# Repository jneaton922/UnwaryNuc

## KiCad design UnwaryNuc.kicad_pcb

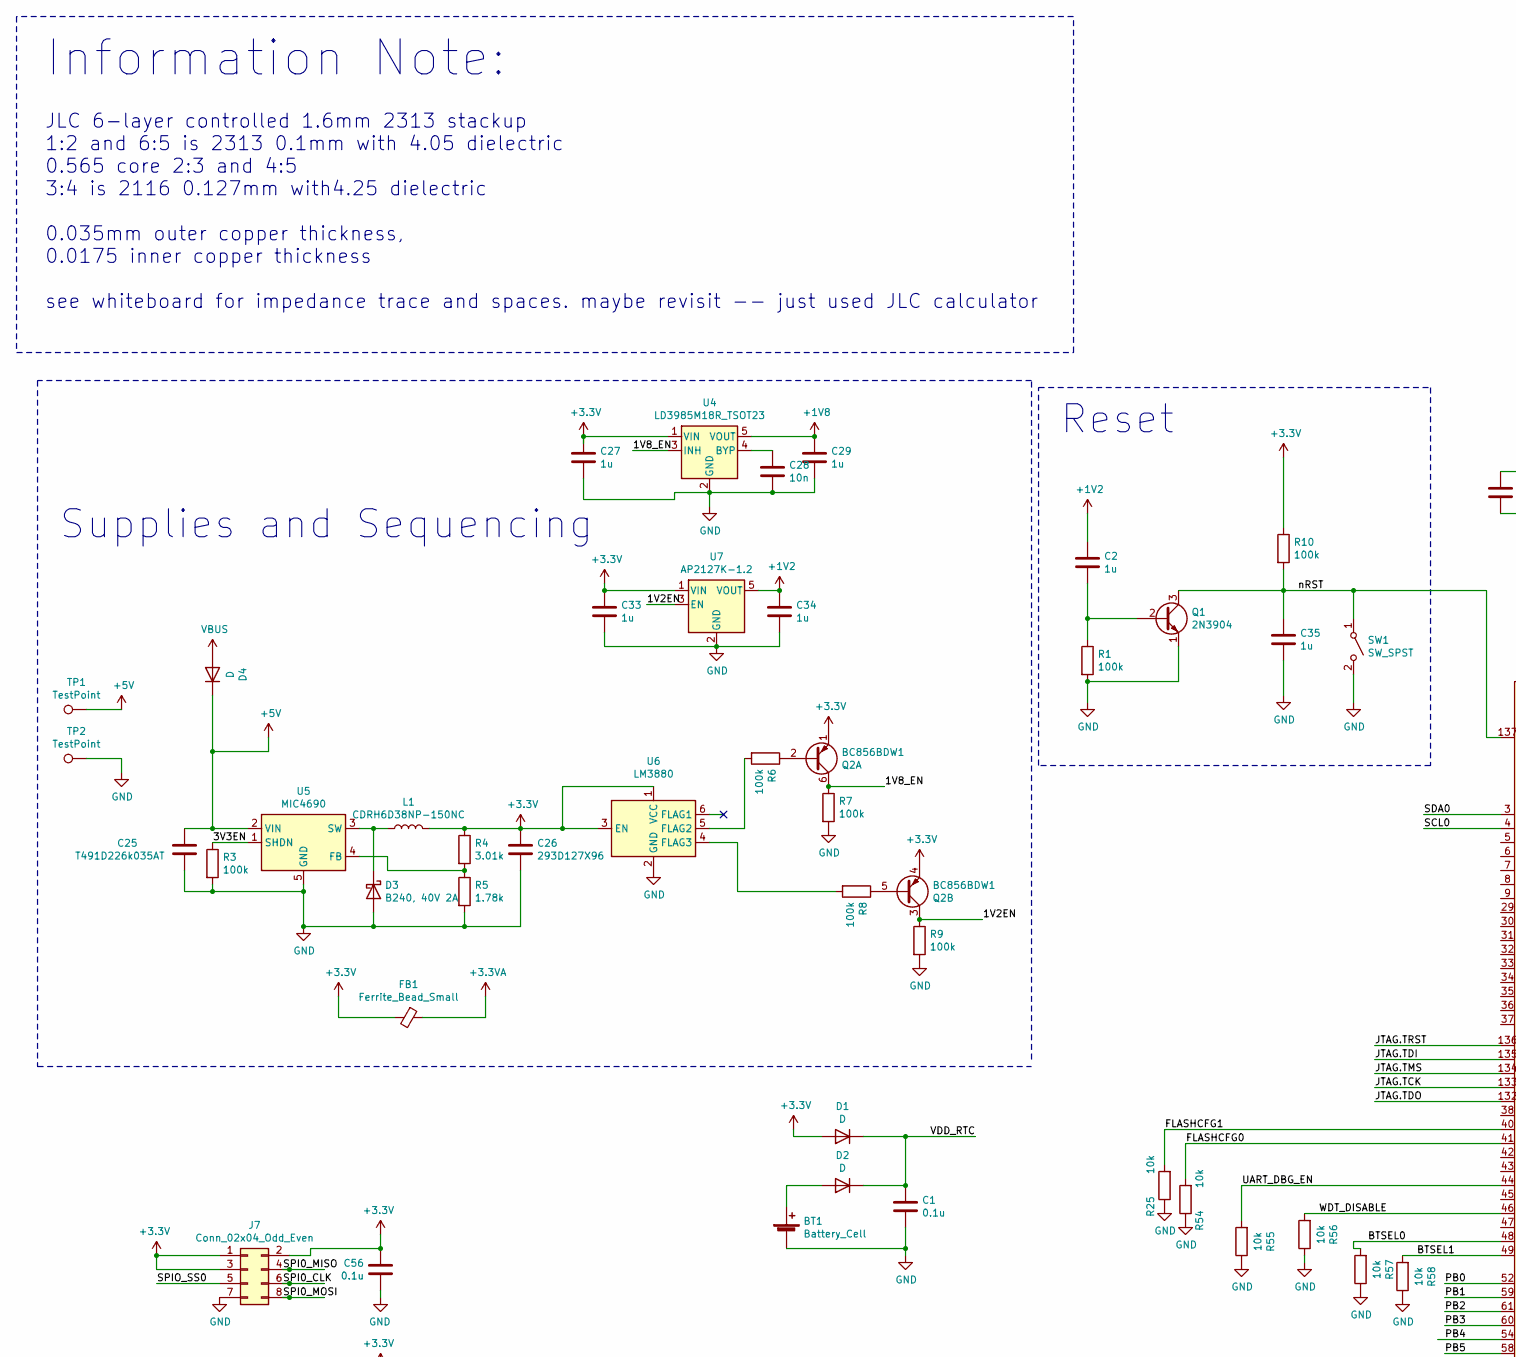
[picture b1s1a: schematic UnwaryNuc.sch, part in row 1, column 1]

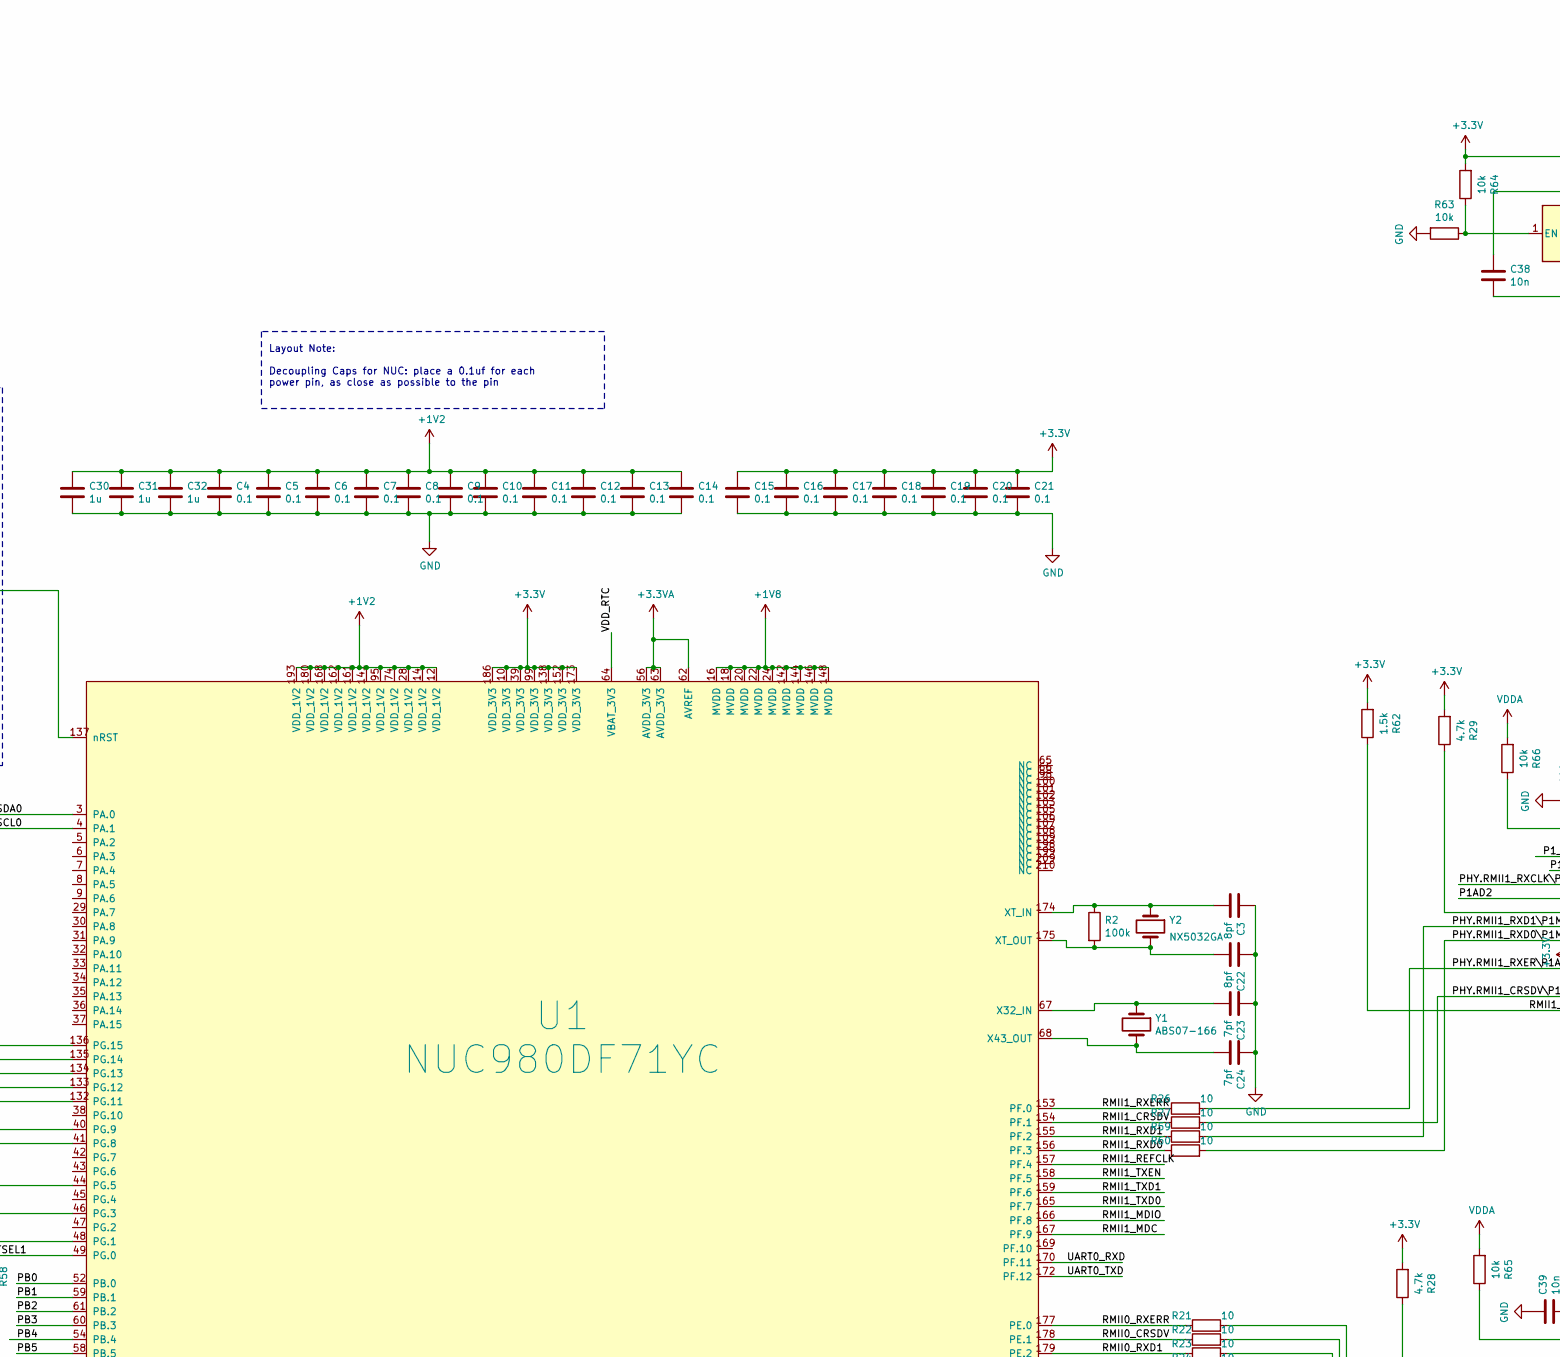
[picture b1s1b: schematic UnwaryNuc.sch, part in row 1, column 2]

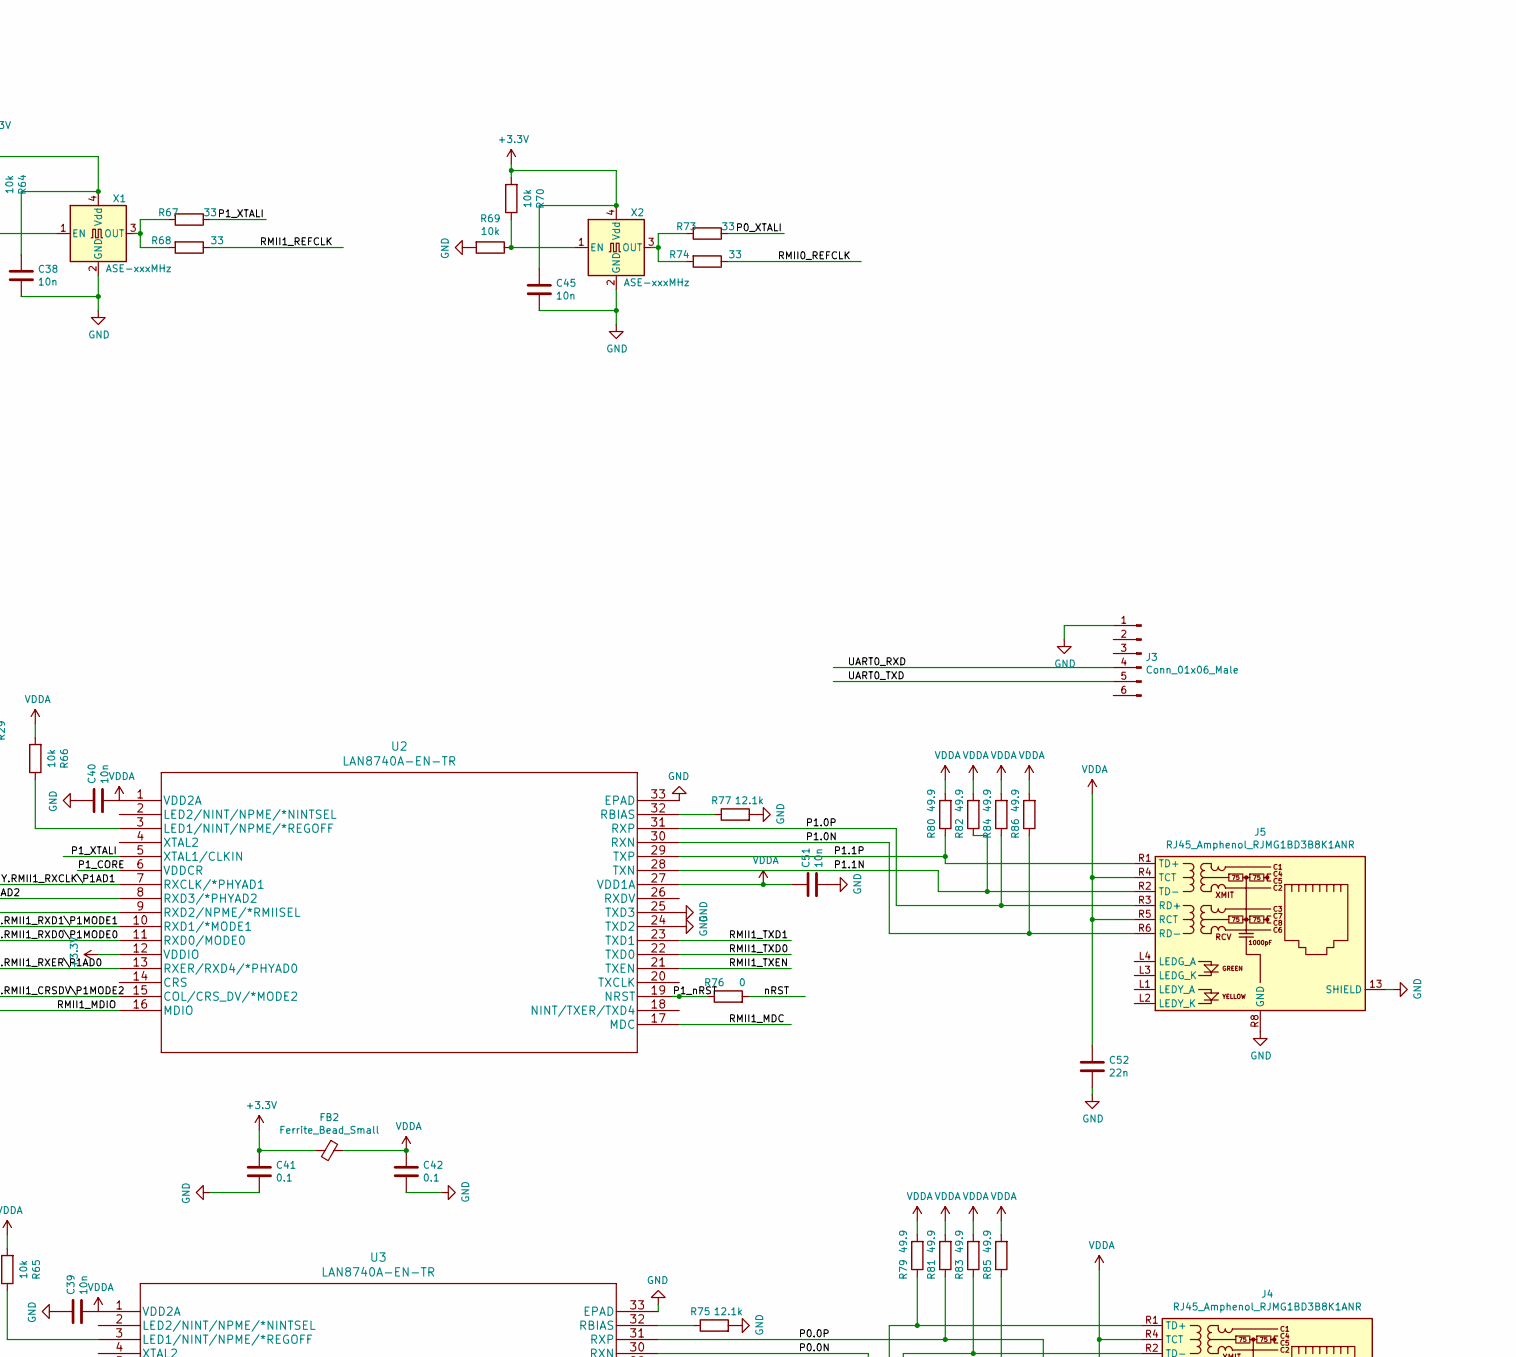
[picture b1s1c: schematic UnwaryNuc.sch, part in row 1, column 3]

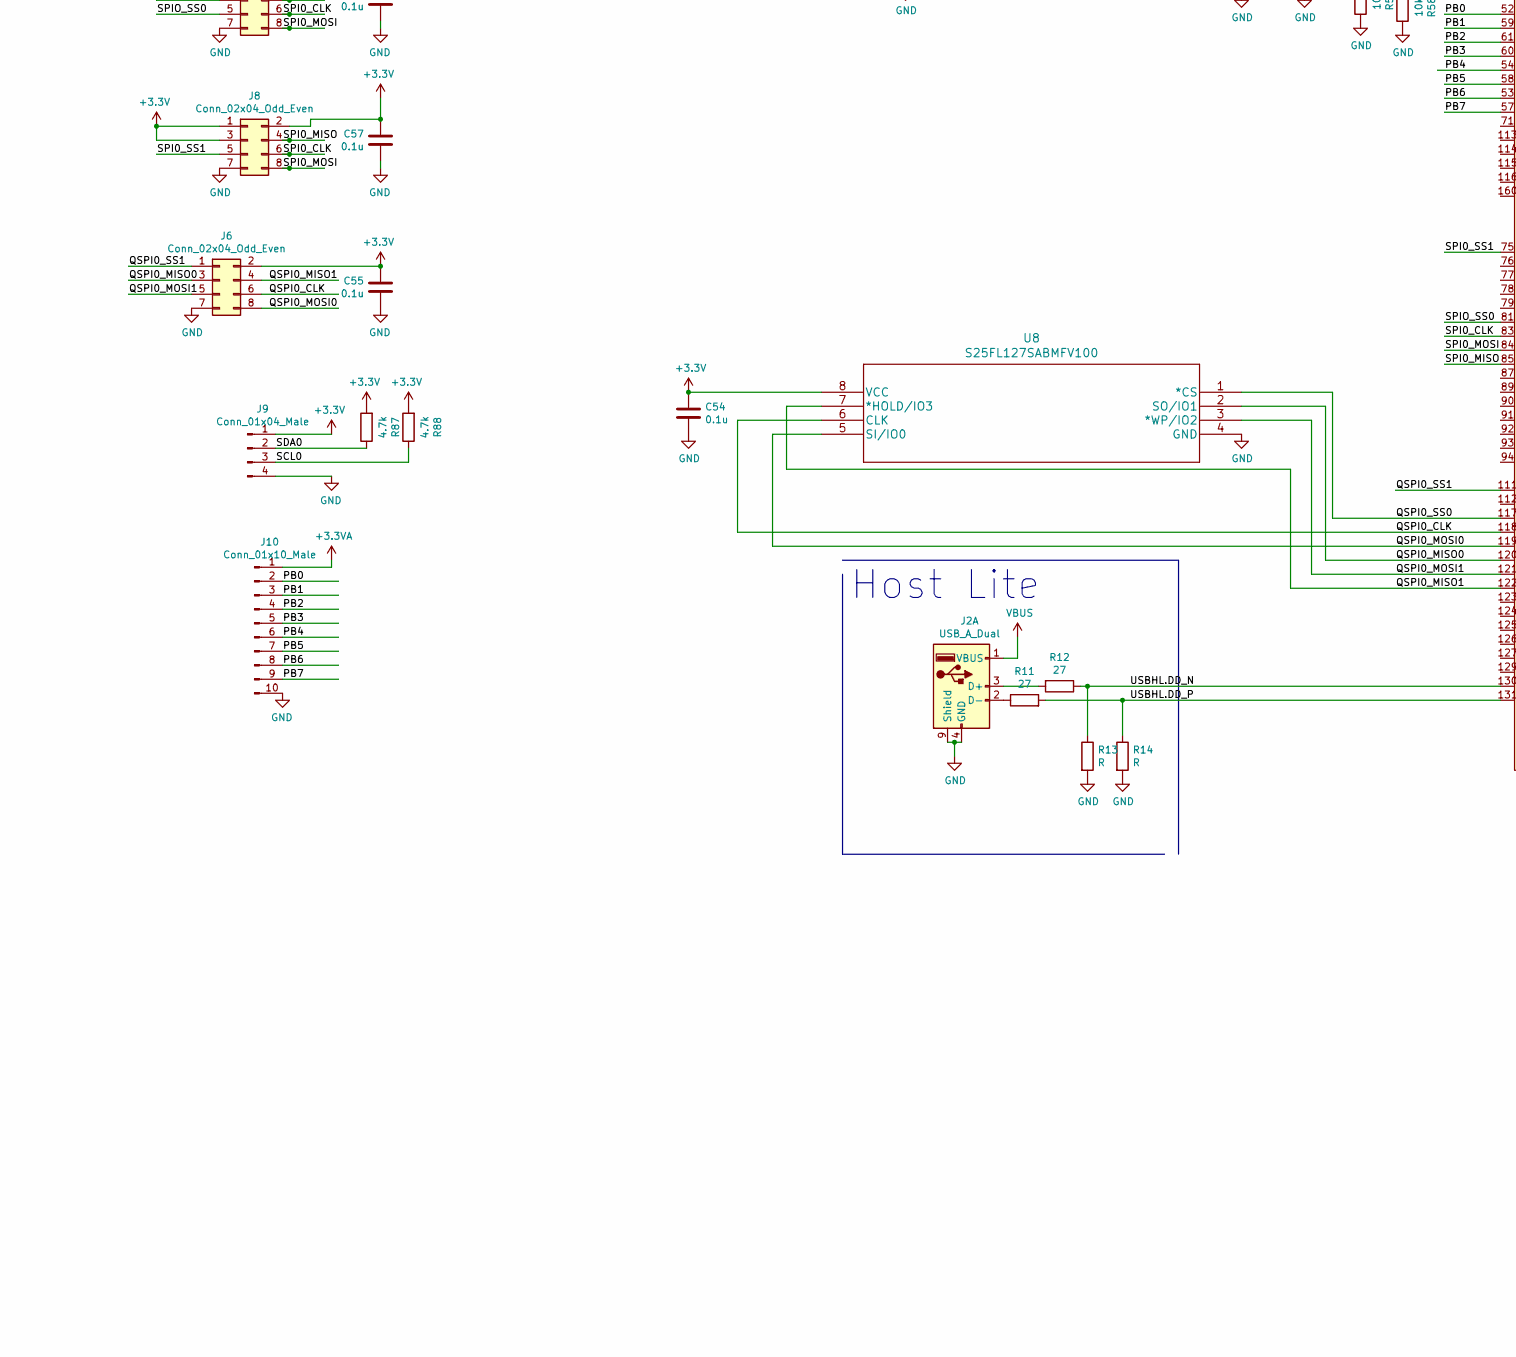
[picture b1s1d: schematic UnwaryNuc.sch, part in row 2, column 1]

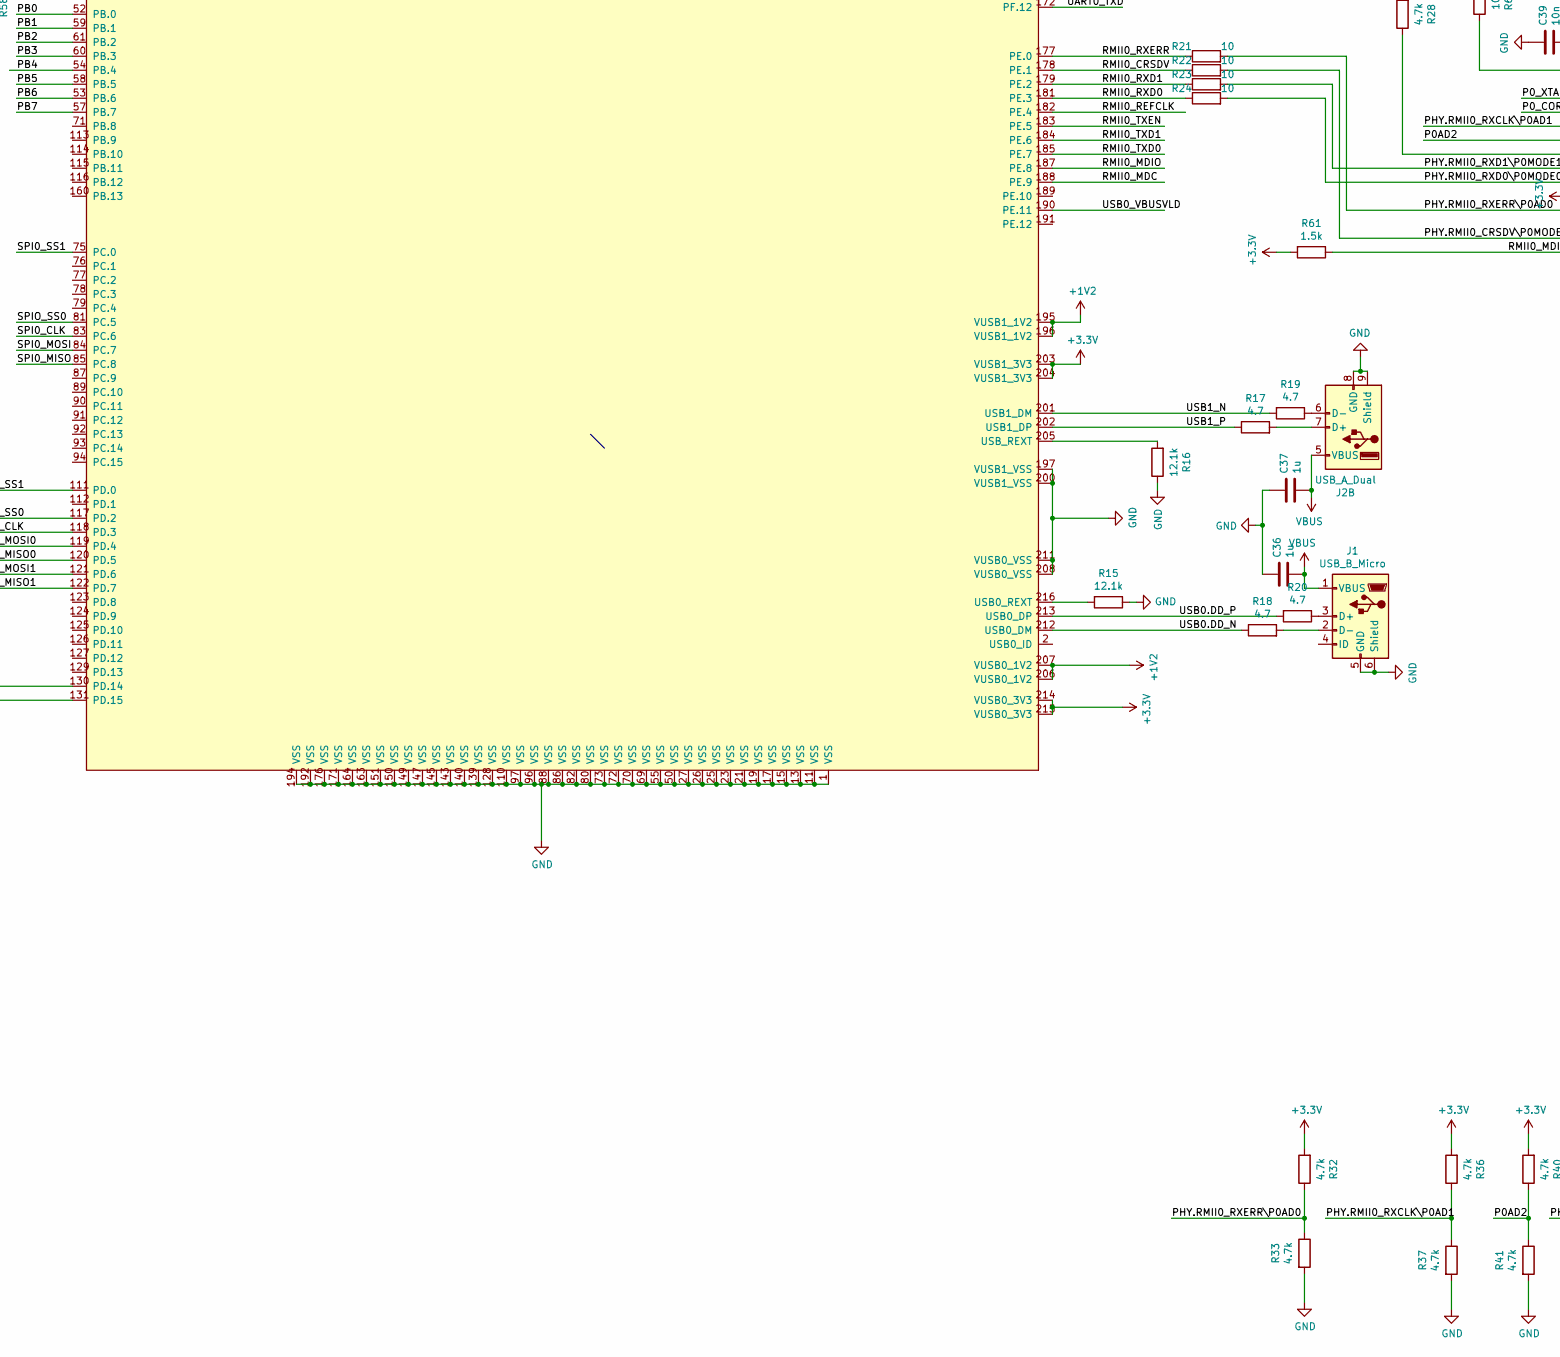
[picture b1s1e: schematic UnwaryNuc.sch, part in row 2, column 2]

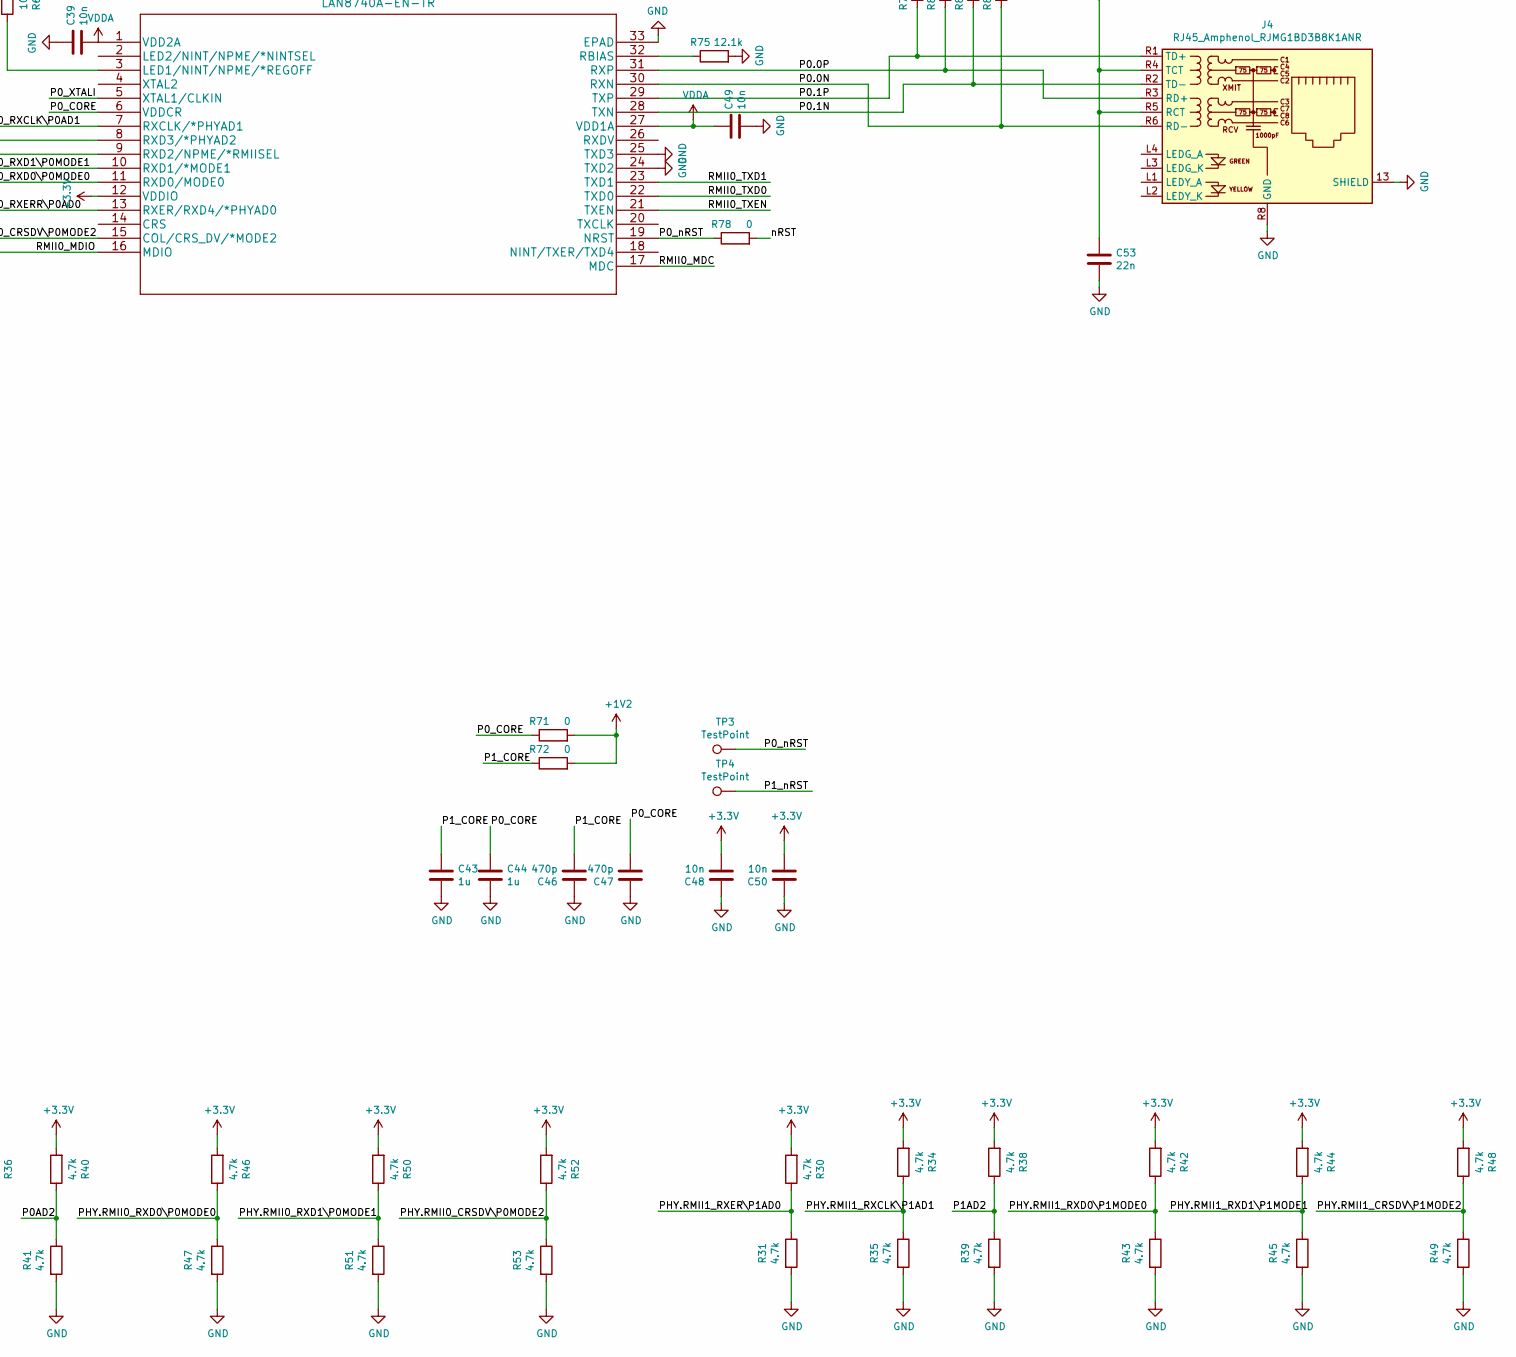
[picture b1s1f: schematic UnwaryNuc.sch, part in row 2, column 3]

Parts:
BT1: Battery_Cell; Battery_Panasonic_CR2032-VS1N_Vertical_CircularHoles
C1, C54, C55, C56, C57: 0.1u; C_1206_3216Metric_Pad1.33x1.80mm_HandSolder
C2, C27, C29, C30, C31, C32, C33, C34, C35, C36, C37, C43, C44: 1u; C_1206_3216Metric_Pad1.33x1.80mm_HandSolder
C3, C22: 8pf; C_0603_1608Metric_Pad1.08x0.95mm_HandSolder
C4, C5, C6, C7, C8, C9, C10, C11, C12, C13, C14, C15, C16, C17, C18, C19, C20, C21, C41, C42: 0.1; C_1206_3216Metric_Pad1.33x1.80mm_HandSolder
C23, C24: 7pf; C_0603_1608Metric_Pad1.08x0.95mm_HandSolder
C25: T491D226k035AT; CP_EIA-7343-15_Kemet-W_Pad2.25x2.55mm_HandSolder
C26: 293D127X96; CP_EIA-7343-43_Kemet-X_Pad2.25x2.55mm_HandSolder
C28: 10n; C_1206_3216Metric_Pad1.33x1.80mm_HandSolder
C38, C39, C40, C45, C48, C49, C50, C51: 10n; C_0603_1608Metric_Pad1.08x0.95mm_HandSolder
C46, C47: 470p; C_0603_1608Metric_Pad1.08x0.95mm_HandSolder
C52, C53: 22n; C_0805_2012Metric_Pad1.18x1.45mm_HandSolder
D1, D2, D4: D; D_SOD-523
D3: B240, 40V 2A; D_SMB_Handsoldering
FB1, FB2: Ferrite_Bead_Small; L_1206_3216Metric_Pad1.42x1.75mm_HandSolder
J1: USB_B_Micro; USB_Micro-B_Molex_47346-0001
J2: USB_A_Dual; USB_A_Wuerth_61400826021_Horizontal_Stacked
J3: Conn_01x06_Male; PinHeader_1x06_P2.54mm_Vertical
J4, J5: RJ45_Amphenol_RJMG1BD3B8K1ANR
J6, J7, J8: Conn_02x04_Odd_Even; PinHeader_2x04_P2.54mm_Vertical
J9: Conn_01x04_Male; PinHeader_1x04_P2.54mm_Vertical
J10: Conn_01x10_Male; PinHeader_1x10_P2.54mm_Vertical
L1: CDRH6D38NP-150NC; CDRH6D38_Sumida
Q1: 2N3904; TO-92_Inline
Q2: BC856BDW1; SOT-363_SC-70-6
R1, R2, R3, R6, R7, R8, R9, R10: 100k; R_0805_2012Metric_Pad1.20x1.40mm_HandSolder
R4: 3.01k; R_0805_2012Metric_Pad1.20x1.40mm_HandSolder
R5: 1.78k; R_0805_2012Metric_Pad1.20x1.40mm_HandSolder
R11, R12: 27; R_0603_1608Metric_Pad0.98x0.95mm_HandSolder
R13, R14: R; R_0603_1608Metric_Pad0.98x0.95mm_HandSolder
R15, R16, R75, R77: 12.1k; R_0603_1608Metric_Pad0.98x0.95mm_HandSolder
R17, R18, R19, R20: 4.7; R_0603_1608Metric_Pad0.98x0.95mm_HandSolder
R21, R22, R23, R24, R26, R27, R59, R60: 10; R_0603_1608Metric_Pad0.98x0.95mm_HandSolder
R25, R54, R55, R56, R57, R58, R63, R64, R65, R66, R69, R70: 10k; R_0603_1608Metric_Pad0.98x0.95mm_HandSolder
R28, R29, R30, R31, R32, R33, R34, R35, R36, R37, R38, R39, R40, R41, R42, R43, R44, R45, R46, R47, R48, R49, R50, R51, R52, R53, R87, R88: 4.7k; R_0603_1608Metric_Pad0.98x0.95mm_HandSolder
R61, R62: 1.5k; R_0603_1608Metric_Pad0.98x0.95mm_HandSolder
R67, R68, R73, R74: 33; R_0603_1608Metric_Pad0.98x0.95mm_HandSolder
R71, R72: 0; R_0805_2012Metric_Pad1.20x1.40mm_HandSolder
R76, R78: 0; R_0603_1608Metric_Pad0.98x0.95mm_HandSolder
R79, R80, R81, R82, R83, R84, R85, R86: 49.9; R_0603_1608Metric_Pad0.98x0.95mm_HandSolder
SW1: SW_SPST; SW_SPST_CK_RS282G05A3
TP1, TP2, TP3, TP4: TestPoint; TestPoint_Keystone_5019_Minature
U1: NUC980DF71YC
U2, U3: LAN8740A-EN-TR
U4: LD3985M18R_TSOT23; TSOT-23-5_HandSoldering
U5: MIC4690; SOIC-8_3.9x4.9mm_P1.27mm
U6: LM3880; SOT-23-6
U7: AP2127K-1.2; SOT-23-5
U8: S25FL127SABMFV100
X1, X2: ASE-xxxMHz; Oscillator_SMD_Abracon_ASE-4Pin_3.2x2.5mm
Y1: ABS07-166; Crystal_SMD_3215-2Pin_3.2x1.5mm
Y2: NX5032GA; Crystal_SMD_5032-2Pin_5.0x3.2mm_HandSoldering

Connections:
+1V2: C2.1, C4.1, C5.1, C6.1, C7.1, C8.1, C9.1, C10.1, C11.1, C12.1, C13.1, C14.1, C30.1, C31.1, C32.1, C34.1, R71.2, R72.2, U1.12 (VDD_1V2), U1.14 (VDD_1V2), U1.28 (VDD_1V2), U1.74 (VDD_1V2), U1.95 (VDD_1V2), U1.141 (VDD_1V2), U1.161 (VDD_1V2), U1.162 (VDD_1V2), U1.168 (VDD_1V2), U1.180 (VDD_1V2), U1.193 (VDD_1V2), U1.195 (VUSB1_1V2), U1.196 (VUSB1_1V2), U1.206 (VUSB0_1V2), U1.207 (VUSB0_1V2), U7.5 (VOUT)
+1V8: C29.1, U1.16 (MVDD), U1.18 (MVDD), U1.20 (MVDD), U1.22 (MVDD), U1.24 (MVDD), U1.142 (MVDD), U1.144 (MVDD), U1.146 (MVDD), U1.148 (MVDD), U4.5 (VOUT)
+3.3VA: FB1.1, J10.1, U1.56 (AVDD_3V3), U1.62 (AVREF), U1.63 (AVDD_3V3)
+3V3: C15.1, C16.1, C17.1, C18.1, C19.1, C20.1, C21.1, C26.1, C27.1, C33.1, C38.1, C41.1, C45.1, C48.2, C50.2, C54.1, C55.1, C56.1, C57.1, D1.2 (A), FB1.2, FB2.2, J6.2, J7.1, J7.2, J7.3, J8.1, J8.2, J8.3, J9.1, L1.2, Q2.1 (E1), Q2.4 (E2), R4.1, R10.1, R28.2, R29.2, R30.2, R32.2, R34.2, R36.2, R38.2, R40.2, R42.2, R44.2, R46.2, R48.2, R50.2, R52.2, R61.2, R62.2, R64.2, R70.2, R87.2, R88.2, U1.10 (VDD_3V3), U1.39 (VDD_3V3), U1.99 (VDD_3V3), U1.138 (VDD_3V3), U1.152 (VDD_3V3), U1.173 (VDD_3V3), U1.186 (VDD_3V3), U1.203 (VUSB1_3V3), U1.204 (VUSB1_3V3), U1.214 (VUSB0_3V3), U1.215 (VUSB0_3V3), U2.12 (VDDIO), U3.12 (VDDIO), U4.1 (VIN), U6.1 (VCC), U6.3 (EN), U7.1 (VIN), U8.8 (VCC), X1.4 (Vdd), X2.4 (Vdd)
+5V: C25.1, D4.1 (K), TP1.1, U5.2 (VIN)
/1V2EN: Q2.3 (C2), R9.1, U7.3 (EN)
/1V8_EN: Q2.6 (C1), R7.1, U4.3 (INH)
/3V3EN: R3.1, U5.1 (SHDN)
/BTSEL0: R57.2, U1.48 (PG.1)
/BTSEL1: R58.2, U1.49 (PG.0)
/FLASHCFG0: R54.2, U1.41 (PG.8)
/FLASHCFG1: R25.2, U1.40 (PG.9)
/JTAG.TCK: U1.133 (PG.12)
/JTAG.TDI: U1.135 (PG.14)
/JTAG.TDO: U1.132 (PG.11)
/JTAG.TMS: U1.134 (PG.13)
/JTAG.TRST: U1.136 (PG.15)
/P0.0N: J4.R6 (RD-), R85.1, U3.30 (RXN)
/P0.0P: J4.R3 (RD+), R81.1, U3.31 (RXP)
/P0.1N: J4.R2 (TD-), R83.1, U3.28 (TXN)
/P0.1P: J4.R1 (TD+), R79.1, U3.29 (TXP)
/P0AD2: R40.1, R41.1, U3.8 (RXD3/*PHYAD2)
/P0_CORE: C44.1, C47.2, R71.1, U3.6 (VDDCR)
/P0_XTALI: R73.1, U3.5 (XTAL1/CLKIN)
/P0_nRST: R78.1, TP3.1, U3.19 (NRST)
/P1.0N: J5.R6 (RD-), R86.1, U2.30 (RXN)
/P1.0P: J5.R3 (RD+), R84.1, U2.31 (RXP)
/P1.1N: J5.R2 (TD-), R82.1, U2.28 (TXN)
/P1.1P: J5.R1 (TD+), R80.1, U2.29 (TXP)
/P1AD2: R38.1, R39.1, U2.8 (RXD3/*PHYAD2)
/P1_CORE: C43.1, C46.2, R72.1, U2.6 (VDDCR)
/P1_XTALI: R67.1, U2.5 (XTAL1/CLKIN)
/P1_nRST: R76.1, TP4.1, U2.19 (NRST)
/PB0: J10.2, U1.52 (PB.0)
/PB1: J10.3, U1.59 (PB.1)
/PB2: J10.4, U1.61 (PB.2)
/PB3: J10.5, U1.60 (PB.3)
/PB4: J10.6, U1.54 (PB.4)
/PB5: J10.7, U1.58 (PB.5)
/PB6: J10.8, U1.53 (PB.6)
/PB7: J10.9, U1.57 (PB.7)
/PHY.RMII0_CRSDV\P0MODE2: R22.2, R52.1, R53.1, U3.15 (COL/CRS_DV/*MODE2)
/PHY.RMII0_RXCLK\P0AD1: R36.1, R37.1, U3.7 (RXCLK/*PHYAD1)
/PHY.RMII0_RXD0\P0MODE0: R24.2, R46.1, R47.1, U3.11 (RXD0/MODE0)
/PHY.RMII0_RXD1\P0MODE1: R23.2, R50.1, R51.1, U3.10 (RXD1/*MODE1)
/PHY.RMII0_RXERR\P0AD0: R21.2, R32.1, R33.1, U3.13 (RXER/RXD4/*PHYAD0)
/PHY.RMII1_CRSDV\P1MODE2: R27.2, R48.1, R49.1, U2.15 (COL/CRS_DV/*MODE2)
/PHY.RMII1_RXCLK\P1AD1: R34.1, R35.1, U2.7 (RXCLK/*PHYAD1)
/PHY.RMII1_RXD0\P1MODE0: R42.1, R43.1, R60.2, U2.11 (RXD0/MODE0)
/PHY.RMII1_RXD1\P1MODE1: R44.1, R45.1, R59.2, U2.10 (RXD1/*MODE1)
/PHY.RMII1_RXER\P1AD0: R26.2, R30.1, R31.1, U2.13 (RXER/RXD4/*PHYAD0)
/QSPI0_CLK: J6.6, U1.118 (PD.3), U8.6 (CLK)
/QSPI0_MISO0: J6.3, U1.120 (PD.5), U8.2 (SO/IO1)
/QSPI0_MISO1: J6.4, U1.122 (PD.7), U8.7 (*HOLD/IO3)
/QSPI0_MOSI0: J6.8, U1.119 (PD.4), U8.5 (SI/IO0)
/QSPI0_MOSI1: J6.5, U1.121 (PD.6), U8.3 (*WP/IO2)
/QSPI0_SS0: U1.117 (PD.2), U8.1 (*CS)
/QSPI0_SS1: J6.1, U1.111 (PD.0)
/RMII0_CRSDV: R22.1, U1.178 (PE.1)
/RMII0_MDC: U1.188 (PE.9), U3.17 (MDC)
/RMII0_MDIO: R61.1, U1.187 (PE.8), U3.16 (MDIO)
/RMII0_REFCLK: R74.1, U1.182 (PE.4)
/RMII0_RXD0: R24.1, U1.181 (PE.3)
/RMII0_RXD1: R23.1, U1.179 (PE.2)
/RMII0_RXERR: R21.1, U1.177 (PE.0)
/RMII0_TXD0: U1.185 (PE.7), U3.22 (TXD0)
/RMII0_TXD1: U1.184 (PE.6), U3.23 (TXD1)
/RMII0_TXEN: U1.183 (PE.5), U3.21 (TXEN)
/RMII1_CRSDV: R27.1, U1.154 (PF.1)
/RMII1_MDC: U1.167 (PF.9), U2.17 (MDC)
/RMII1_MDIO: R62.1, U1.166 (PF.8), U2.16 (MDIO)
/RMII1_REFCLK: R68.1, U1.157 (PF.4)
/RMII1_RXD0: R60.1, U1.156 (PF.3)
/RMII1_RXD1: R59.1, U1.155 (PF.2)
/RMII1_RXERR: R26.1, U1.153 (PF.0)
/RMII1_TXD0: U1.165 (PF.7), U2.22 (TXD0)
/RMII1_TXD1: U1.159 (PF.6), U2.23 (TXD1)
/RMII1_TXEN: U1.158 (PF.5), U2.21 (TXEN)
/SCL0: J9.3, R88.1, U1.4 (PA.1)
/SDA0: J9.2, R87.1, U1.3 (PA.0)
/SPI0_CLK: J7.6, J8.6, U1.83 (PC.6)
/SPI0_MISO: J7.4, J8.4, U1.85 (PC.8)
/SPI0_MOSI: J7.8, J8.8, U1.84 (PC.7)
/SPI0_SS1: J8.5, U1.75 (PC.0)
/SPIO_SS0: J7.5, U1.81 (PC.5)
/UART0_RXD: J3.4, U1.170 (PF.11)
/UART0_TXD: J3.5, U1.172 (PF.12)
/UART_DBG_EN: R55.2, U1.44 (PG.5)
/USB0.DD_N: R18.1, U1.212 (USB0_DM)
/USB0.DD_P: R20.2, U1.213 (USB0_DP)
/USB0_VBUSVLD: U1.190 (PE.11)
/USB1_N: R19.2, U1.201 (USB1_DM)
/USB1_P: R17.1, U1.202 (USB1_DP)
/USBHL.DD_N: R12.1, R13.1, U1.130 (PD.14)
/USBHL.DD_P: R11.2, R14.1, U1.131 (PD.15)
/VDD_RTC: C1.1, D1.1 (K), D2.1 (K), U1.64 (VBAT_3V3)
/WDT_DISABLE: R56.2, U1.46 (PG.3)
/nRST: C35.1, Q1.3 (C), R10.2, R76.2, R78.2, SW1.1 (A), U1.137 (nRST)
GND: BT1.2 (-), C1.2, C3.1, C4.2, C5.2, C6.2, C7.2, C8.2, C9.2, C10.2, C11.2, C12.2, C13.2, C14.2, C15.2, C16.2, C17.2, C18.2, C19.2, C20.2, C21.2, C22.1, C23.1, C24.1, C25.2, C26.2, C27.2, C28.2, C29.2, C30.2, C31.2, C32.2, C33.2, C34.2, C35.2, C36.1, C37.1, C38.2, C39.1, C40.1, C41.2, C42.2, C43.2, C44.2, C45.2, C46.1, C47.1, C48.1, C49.2, C50.1, C51.2, C52.2, C53.2, C54.2, C55.2, C56.2, C57.2, D3.2 (A), J1.5 (GND), J1.6 (Shield), J2.4 (GND), J2.8 (GND), J2.9 (Shield), J3.1, J4.13 (SHIELD), J4.R8 (GND), J5.13 (SHIELD), J5.R8 (GND), J6.7, J7.7, J8.7, J9.4, J10.10, Q1.1 (E), R1.2, R3.2, R5.2, R7.2, R9.2, R13.2, R14.2, R15.1, R16.1, R25.1, R31.2, R33.2, R35.2, R37.2, R39.2, R41.2, R43.2, R45.2, R47.2, R49.2, R51.2, R53.2, R54.1, R55.1, R56.1, R57.1, R58.1, R63.2, R69.2, R75.2, R77.2, SW1.2 (B), TP2.1, U1.1 (VSS), U1.11 (VSS), U1.13 (VSS), U1.15 (VSS), U1.17 (VSS), U1.19 (VSS), U1.21 (VSS), U1.23 (VSS), U1.25 (VSS), U1.26 (VSS), U1.27 (VSS), U1.50 (VSS), U1.55 (VSS), U1.69 (VSS), U1.70 (VSS), U1.72 (VSS), U1.73 (VSS), U1.80 (VSS), U1.82 (VSS), U1.86 (VSS), U1.88 (VSS), U1.96 (VSS), U1.97 (VSS), U1.110 (VSS), U1.128 (VSS), U1.139 (VSS), U1.140 (VSS), U1.143 (VSS), U1.145 (VSS), U1.147 (VSS), U1.149 (VSS), U1.150 (VSS), U1.151 (VSS), U1.163 (VSS), U1.164 (VSS), U1.171 (VSS), U1.176 (VSS), U1.192 (VSS), U1.194 (VSS), U1.197 (VUSB1_VSS), U1.200 (VUSB1_VSS), U1.208 (VUSB0_VSS), U1.211 (VUSB0_VSS), U2.24 (TXD2), U2.25 (TXD3), U2.33 (EPAD), U3.24 (TXD2), U3.25 (TXD3), U3.33 (EPAD), U4.2 (GND), U5.5 (GND), U5.6 (GND), U5.7 (GND), U5.8 (GND), U6.2 (GND), U7.2 (GND), U8.4 (GND), X1.2 (GND), X2.2 (GND)
unnamed: BT1.1 (+), D2.2 (A)
unnamed: C2.2, Q1.2 (B), R1.1
unnamed: C3.2, R2.1, U1.174 (XT_IN), Y2.1
unnamed: C22.2, R2.2, U1.175 (XT_OUT), Y2.2
unnamed: C23.2, U1.67 (X32_IN), Y1.1
unnamed: C24.2, U1.68 (X43_OUT), Y1.2
unnamed: C28.1, U4.4 (BYP)
unnamed: D3.1 (K), L1.1, U5.3 (SW)
unnamed: J1.2 (D-), R18.2
unnamed: J1.3 (D+), R20.1
unnamed: J2.2 (D-), R11.1
unnamed: J2.3 (D+), R12.2
unnamed: J2.6 (D-), R19.1
unnamed: J2.7 (D+), R17.2
unnamed: Q2.2 (B1), R6.1
unnamed: Q2.5 (B2), R8.1
unnamed: R4.2, R5.1, U5.4 (FB)
unnamed: R6.2, U6.5 (FLAG2)
unnamed: R8.2, U6.4 (FLAG3)
unnamed: R15.2, U1.216 (USB0_REXT)
unnamed: R16.2, U1.205 (USB_REXT)
unnamed: R28.1, U3.9 (RXD2/NPME/*RMIISEL)
unnamed: R29.1, U2.9 (RXD2/NPME/*RMIISEL)
unnamed: R63.1, R64.1, X1.1 (EN)
unnamed: R65.1, U3.3 (LED1/NINT/NPME/*REGOFF)
unnamed: R66.1, U2.3 (LED1/NINT/NPME/*REGOFF)
unnamed: R67.2, R68.2, X1.3 (OUT)
unnamed: R69.1, R70.1, X2.1 (EN)
unnamed: R73.2, R74.2, X2.3 (OUT)
unnamed: R75.1, U3.32 (RBIAS)
unnamed: R77.1, U2.32 (RBIAS)
VBUS: C36.2, C37.2, D4.2 (A), J1.1 (VBUS), J2.1 (VBUS), J2.5 (VBUS)
VDDA: C39.2, C40.2, C42.1, C49.1, C51.1, C52.1, C53.1, FB2.1, J4.R4 (TCT), J4.R5 (RCT), J5.R4 (TCT), J5.R5 (RCT), R65.2, R66.2, R79.2, R80.2, R81.2, R82.2, R83.2, R84.2, R85.2, R86.2, U2.1 (VDD2A), U2.27 (VDD1A), U3.1 (VDD2A), U3.27 (VDD1A)

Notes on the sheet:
Information Note:
JLC 6-layer controlled 1.6mm 2313 stackup 1:2 and 6:5 is 2313 0.1mm with 4.05 dielectric 0.565 core 2:3 and 4:5 3:4 is 2116 0.127mm with4.25 dielectric 0.035mm outer copper thickness, 0.0175 inner copper thickness see whiteboard for impedance trace and spaces. maybe revisit -- just used JLC calcula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
Layout Note: Decoupling Caps for NUC: place a 0.1uf for each power pin, as close as possible to the pin
Reset
Supplies and Sequencing
Host Lite

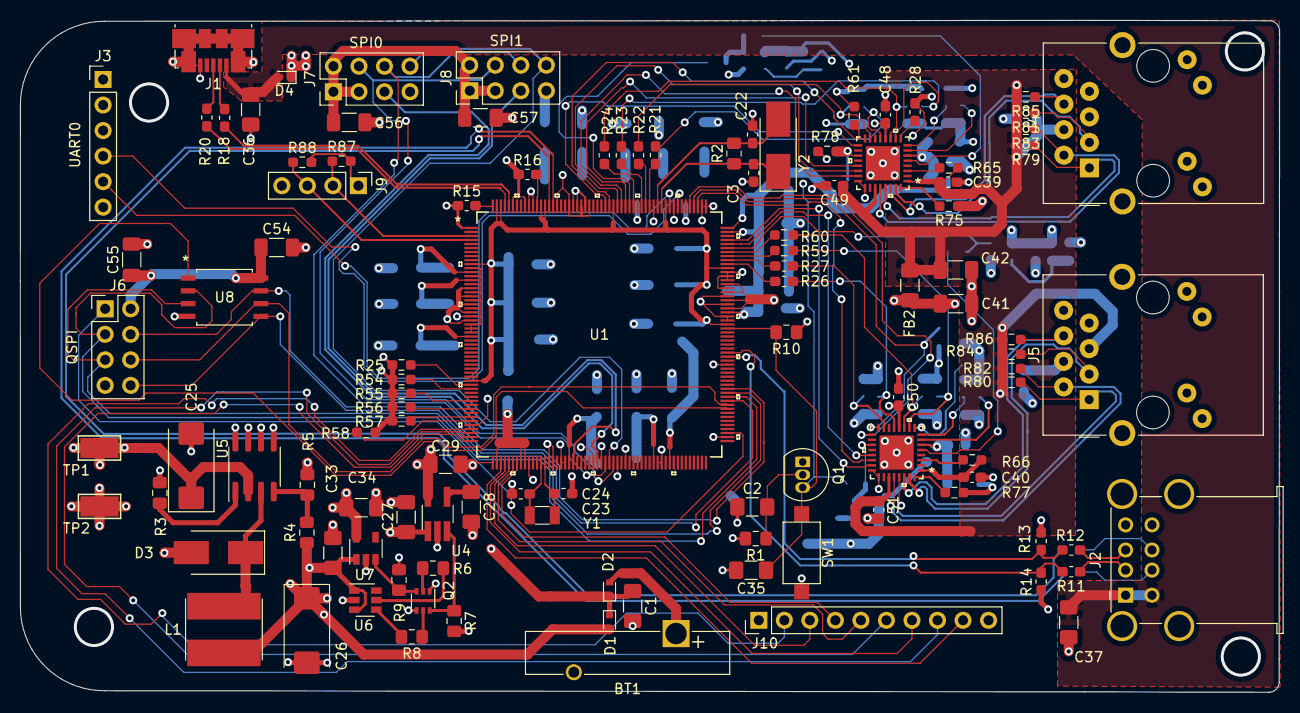
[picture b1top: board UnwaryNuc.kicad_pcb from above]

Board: 4 copper layers, 125.3 x 66.8 mm, 182 parts (0 on the bottom side), 126 nets.

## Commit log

2020-12-30 added some ldos, caps, and reset circuitry.
2020-12-31 added supply sequencing and stuff
2021-04-28 usb's connected, rmii nets assigned, some placement done
2021-06-04 Nuc MAC->PHY->RJ schematic complete, no placement yet
2021-08-02 pushing up to pull to desktop
2021-08-02 updating deprecated library footprints. Sch/pcb back in sync on new system
2021-08-03 Some rough placement grouping and power routing
2021-08-09 added QSPI for boot, routed 1 phy, more placement completed
2021-08-09 started other phy
2021-08-12 Signal routing pretty much done, working out power distribution. Still could/should add Headers for other I/O, and an ESP backpack or something
2021-08-17 finished up some power routing, could still use some cleanup. need to add header for esp and additional GPIO header/expander
2021-08-17 added two spi headers, I2C, and a bank of GPIO. placed, still need routed
2021-08-18 routed SPI0 and SPI1, cleaned up top silk, added some random mounting holes.
2021-08-18 Routed some of PB row, 5 to go.
2021-09-27 finished, board as produced

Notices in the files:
parts and their libraries:
Copyright 2021 Accelerated Designs. All rights reserved.
Copyright 2016 Accelerated Designs. All rights reserved.
